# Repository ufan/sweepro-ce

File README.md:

Sweep-Pro (community edition) is a split keyboard with design focus on:
- smooth and comfortable typing
- minimalism
- portability

# Features #

- wireless using zmk firware, with nrfmicro as MCU module (nrf52840)
- 34+2 keys, with ferris/sweep layout (thumb keys adjusted)
- choc spacing (18x17)
- Kailh choc v1 switches, with hotplug sockets
- two horizontal encoders, with default usage as arrow keys (quick and accurate navigation while editing, best suitied for short-range movement)
- 1.02-inch epd display, with rich status information and excellent power-efficiency
- configurable personal logo on peripheral split's screen
- 160 mAh Li-Po battey, with dedicated slot and hot-plugability
- 3d-printed case, with screen protection
- optional wireless charging module can be integrated

# pcb #
KiCad is used to design the PCB.
The PCB is a two-in-one design, i.e., both left and right split using the same board.
The chirarity is chosen by soldering jumpers on board.

=gerber.zip= can be submitted to the manufacture for production without modification.

# doc #
# case #
The case consists of three seperate parts: top-case, middle-plate and bottom-plate.
FreeCAD is used to design the case.
The source file =case-design.FCStd= contain the design of all parts.
The design is partially parameter-based, with a =parametre= spreadsheet containing all the adjustable parameters.

All parts can be 3D-printed.
The stl files are povided for immediate manufacture without modification.
The design source file can be used to tweak the parameters if needed.

## top-case ##
The top case provides mechanical support for the switches and potection of the epd screen.
It hides all the 'dirty' internals, giving a better appearance of the keyboard comparing common 'open' design.

Three stl models are povided with different height of the epd slot above the PCB: 11.5, 11.6, 11.7.
They are provides since there exists some flexibilty in choosing the components of the epd breakout board and variation of
the soldering result.
It is recommended to measure the height of epd screen (above PCB board + 0.8mm) after assembly and choose the appropiately case.
0.8 mm is the thickness of the screen protection cover.

## middle-plate ##
Juse print the provided stl files, no tweaking is needed.

## bottom-plate ##
Two manufacture methods for the bottom plates:
- 3d print, using the stl models
- laser cut with Acrylic, using the dxf file

It is recommended to use Acrylic as bottom plate for better apperance.

## BOM table ##
[endcoder: EVQWGD001](https://item.taobao.com/item.htm?spm=a1z09.2.0.0.4b012e8dThICYU&id=576827634283&_u=6201h1ah76c85a)
[epd: GoodDisplay 1.02](https://item.taobao.com/item.htm?spm=a1z09.2.0.0.4b012e8dThICYU&id=564905401632&_u=6201h1ah76a92a)

| Component   | Dimension | Quantity |
|:-----------:|:---------:|:--------:|
| M2 screws   | 5 mm      | 20       |
|             | 6 mm      | 20       |
| M2 standoff | 4 mm      | 20       |
|             | 5 mm      | 20       |

# zmk_config #
The official main branck of zmk firmware does not support split encoder, rotated epd screen and other utility features.
These features are available on separate pull requests and they are merged into [the support branch](https://github.com/ufan/zmk/tree/support).
Moreover, a new board called `nrfmacro` and a shield called `sweepro-ce` are defined in this branch.

A reference `zmk_config` [repository](https://github.com/ufan/sweepro-ce_config) is recommended as the starting point for your personal customization.
All the dependency has been correctly defined in this repository, thus you only need to modify the *keymap* file and *conf* file.
The same workflow as recommended by zmk is used, which use GitHub Action to automate firmware building.
Just fork it, make changes, commit.
The firmware is then available for download. For more details of this process, check [the official document](https://zmk.dev/docs/user-setup).

## Build in local environment ##
It's also possible to build the firmware locally.
Prerequisites:
- set up the deveplopment environment, see [official document](https://zmk.dev/docs/development/setup) for the steps
- clone and checkout the `support` branch
- clone the forked `zmk_config` repository
- build using
  - board name: `nrfmacro`
  - shield name: `sweepro-ce_left`, `sweepro-ce_right`

# User guide #
A more detailed user guide is available here, which includes:
- config options specific for the `nrfmacro` board
- explanation of the status screen
- how to customize the personal logo on the right split

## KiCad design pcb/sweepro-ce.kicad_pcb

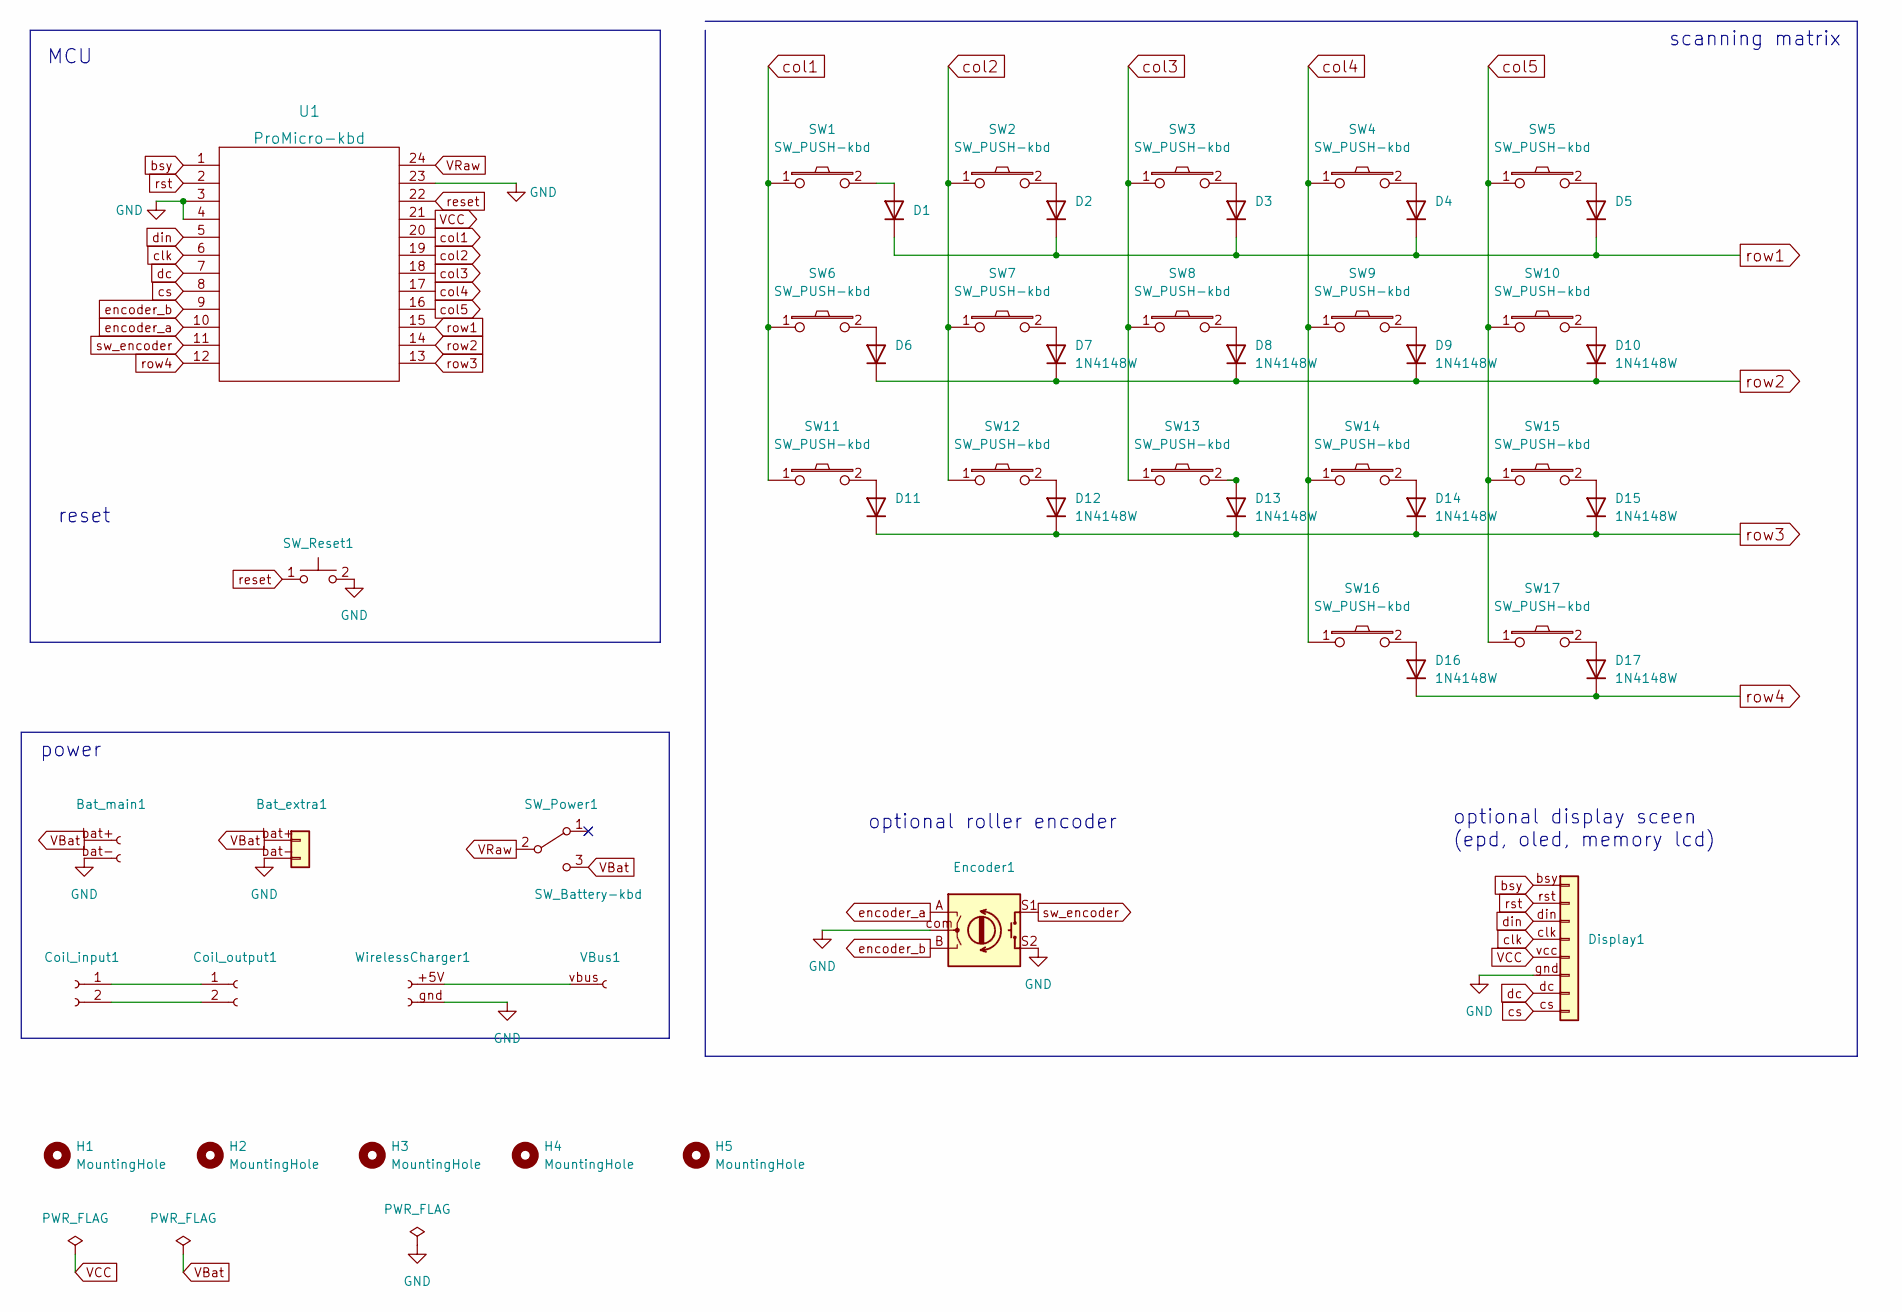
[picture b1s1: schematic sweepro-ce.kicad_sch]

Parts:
Bat_extra1: Conn_Battery_pluggable; Battery_connector_lim_reversible
Bat_main1: Conn_Battery_solderable; Battery_pads_reversible
Coil_input1: Conn_01x02_Female; WirelessChager_pads_reversible
Coil_output1: Conn_01x02_Female; WirelessChager_pads_reversible
D1, D2, D3, D4, D5, D6, D7, D8, D9, D10, D11, D12, D13, D14, D15, D16, D17: 1N4148W; Diode_SOD-123_reversible
Display1: Conn_Display_general; Conn_EPD_Jumper
Encoder1: RotaryEncoder; RollerEncoder_EVQWGD001_reversible
H1, H2, H3, H4: MountingHole; MountingHole_2.2mm_M2_ISO7380_Pad_TopBottom
H5: MountingHole; MountingHole_3.2mm_M3_DIN965
SW1, SW2, SW3, SW4, SW5, SW6, SW7, SW8, SW9, SW10, SW11, SW12, SW13, SW14, SW15, SW16, SW17: SW_PUSH-kbd; Kailh_Choc_Hotplug_reversible
SW_Power1: SW_Battery-kbd; Power_reversible
SW_Reset1: SW_RESET-kbd; SW_Reset_vertical
U1: ProMicro-kbd; ProMicro_Jumpers
VBus1: Conn_01x01_Female; GND_1pin_conn
WirelessCharger1: Conn_01x02_Female; VBus_pad_reversible

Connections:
GND: Bat_extra1.bat- (Bat-), Bat_main1.bat- (Bat-), Display1.gnd (GND), Encoder1.S2, Encoder1.com (COM), SW_Reset1.2, U1.3 (GND), U1.4 (GND), U1.23 (GND), WirelessCharger1.gnd (GND)
unnamed: Coil_input1.1, Coil_output1.1
unnamed: Coil_input1.2, Coil_output1.2
unnamed: D1.2 (A), SW1.2
unnamed: D2.2 (A), SW2.2
unnamed: D3.2 (A), SW3.2
unnamed: D4.2 (A), SW4.2
unnamed: D5.2 (A), SW5.2
unnamed: D6.2 (A), SW6.2
unnamed: D7.2 (A), SW7.2
unnamed: D8.2 (A), SW8.2
unnamed: D9.2 (A), SW9.2
unnamed: D10.2 (A), SW10.2
unnamed: D11.2 (A), SW11.2
unnamed: D12.2 (A), SW12.2
unnamed: D13.2 (A), SW13.2
unnamed: D14.2 (A), SW14.2
unnamed: D15.2 (A), SW15.2
unnamed: D16.2 (A), SW16.2
unnamed: D17.2 (A), SW17.2
unnamed: VBus1.vbus (VBus), WirelessCharger1.+5V
VBat: Bat_extra1.bat+ (Bat+), Bat_main1.bat+ (Bat+), SW_Power1.3 (C)
VCC: Display1.vcc (VCC), U1.21 (VCC)
VRaw: SW_Power1.2 (B), U1.24 (RAW)
bsy: Display1.bsy (BSY), U1.1 (TX)
clk: Display1.clk (CLK), U1.6 (SCL)
col1: SW1.1, SW6.1, SW11.1, U1.20 (F4)
col2: SW2.1, SW7.1, SW12.1, U1.19 (F5)
col3: SW3.1, SW8.1, SW13.1, U1.18 (F6)
col4: SW4.1, SW9.1, SW14.1, SW16.1, U1.17 (F7)
col5: SW5.1, SW10.1, SW15.1, SW17.1, U1.16 (B1)
cs: Display1.cs (CS), U1.8 (C6)
dc: Display1.dc (DC), U1.7 (D4)
din: Display1.din (DIN), U1.5 (SDA)
encoder_a: Encoder1.A, U1.10 (E6)
encoder_b: Encoder1.B, U1.9 (D7)
reset: SW_Reset1.1, U1.22 (RST)
row1: D1.1 (K), D2.1 (K), D3.1 (K), D4.1 (K), D5.1 (K), U1.15 (B3)
row2: D6.1 (K), D7.1 (K), D8.1 (K), D9.1 (K), D10.1 (K), U1.14 (B2)
row3: D11.1 (K), D12.1 (K), D13.1 (K), D14.1 (K), D15.1 (K), U1.13 (B6)
row4: D16.1 (K), D17.1 (K), U1.12 (B5)
rst: Display1.rst (RST), U1.2 (RX)
sw_encoder: Encoder1.S1, U1.11 (B4)

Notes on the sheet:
scanning matrix
optional roller encoder
reset
power
optional display sceen (epd, oled, memory lcd)
MCU

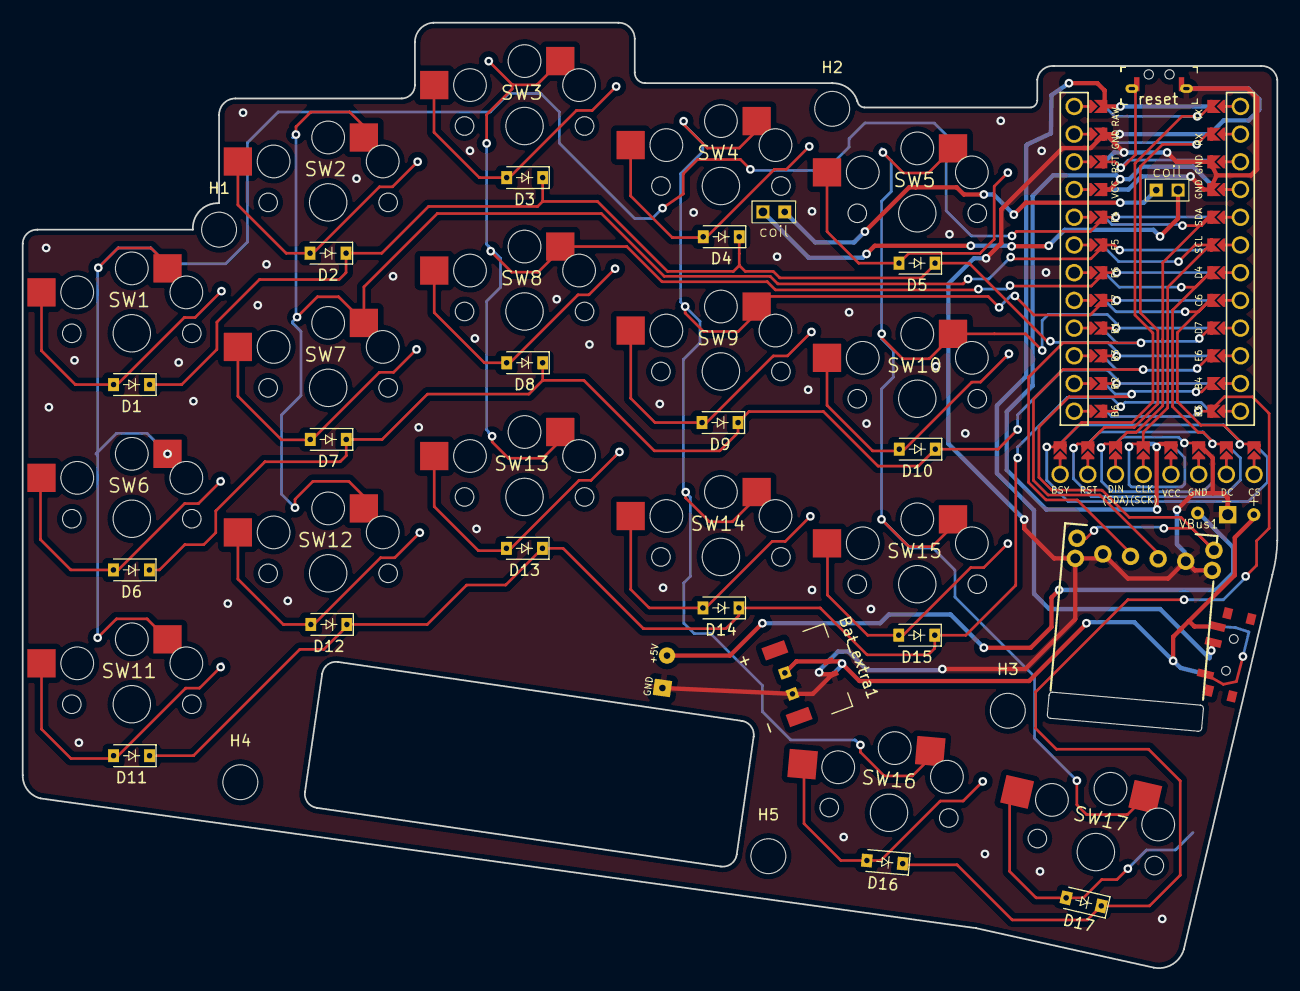
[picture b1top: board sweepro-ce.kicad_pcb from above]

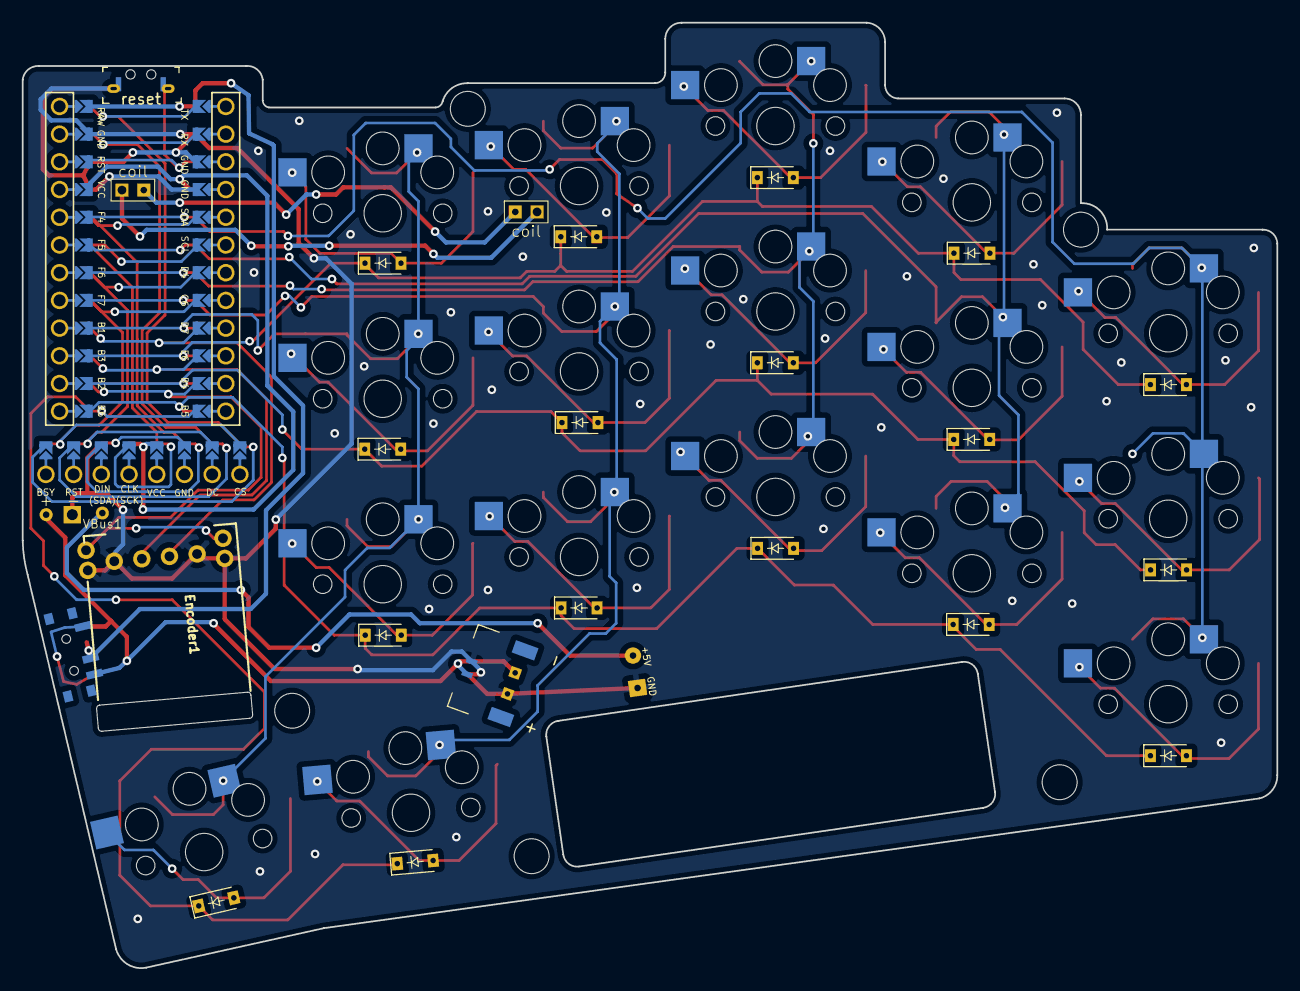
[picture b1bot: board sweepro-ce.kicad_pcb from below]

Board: 2 copper layers, 115.0 x 86.7 mm, 50 parts (2 on the bottom side), 43 nets.

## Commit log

2022-07-15 add all case files
2022-07-18 backup
